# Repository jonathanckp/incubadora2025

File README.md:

# incubadora2025
proyecto incubadora de huevos - 2025

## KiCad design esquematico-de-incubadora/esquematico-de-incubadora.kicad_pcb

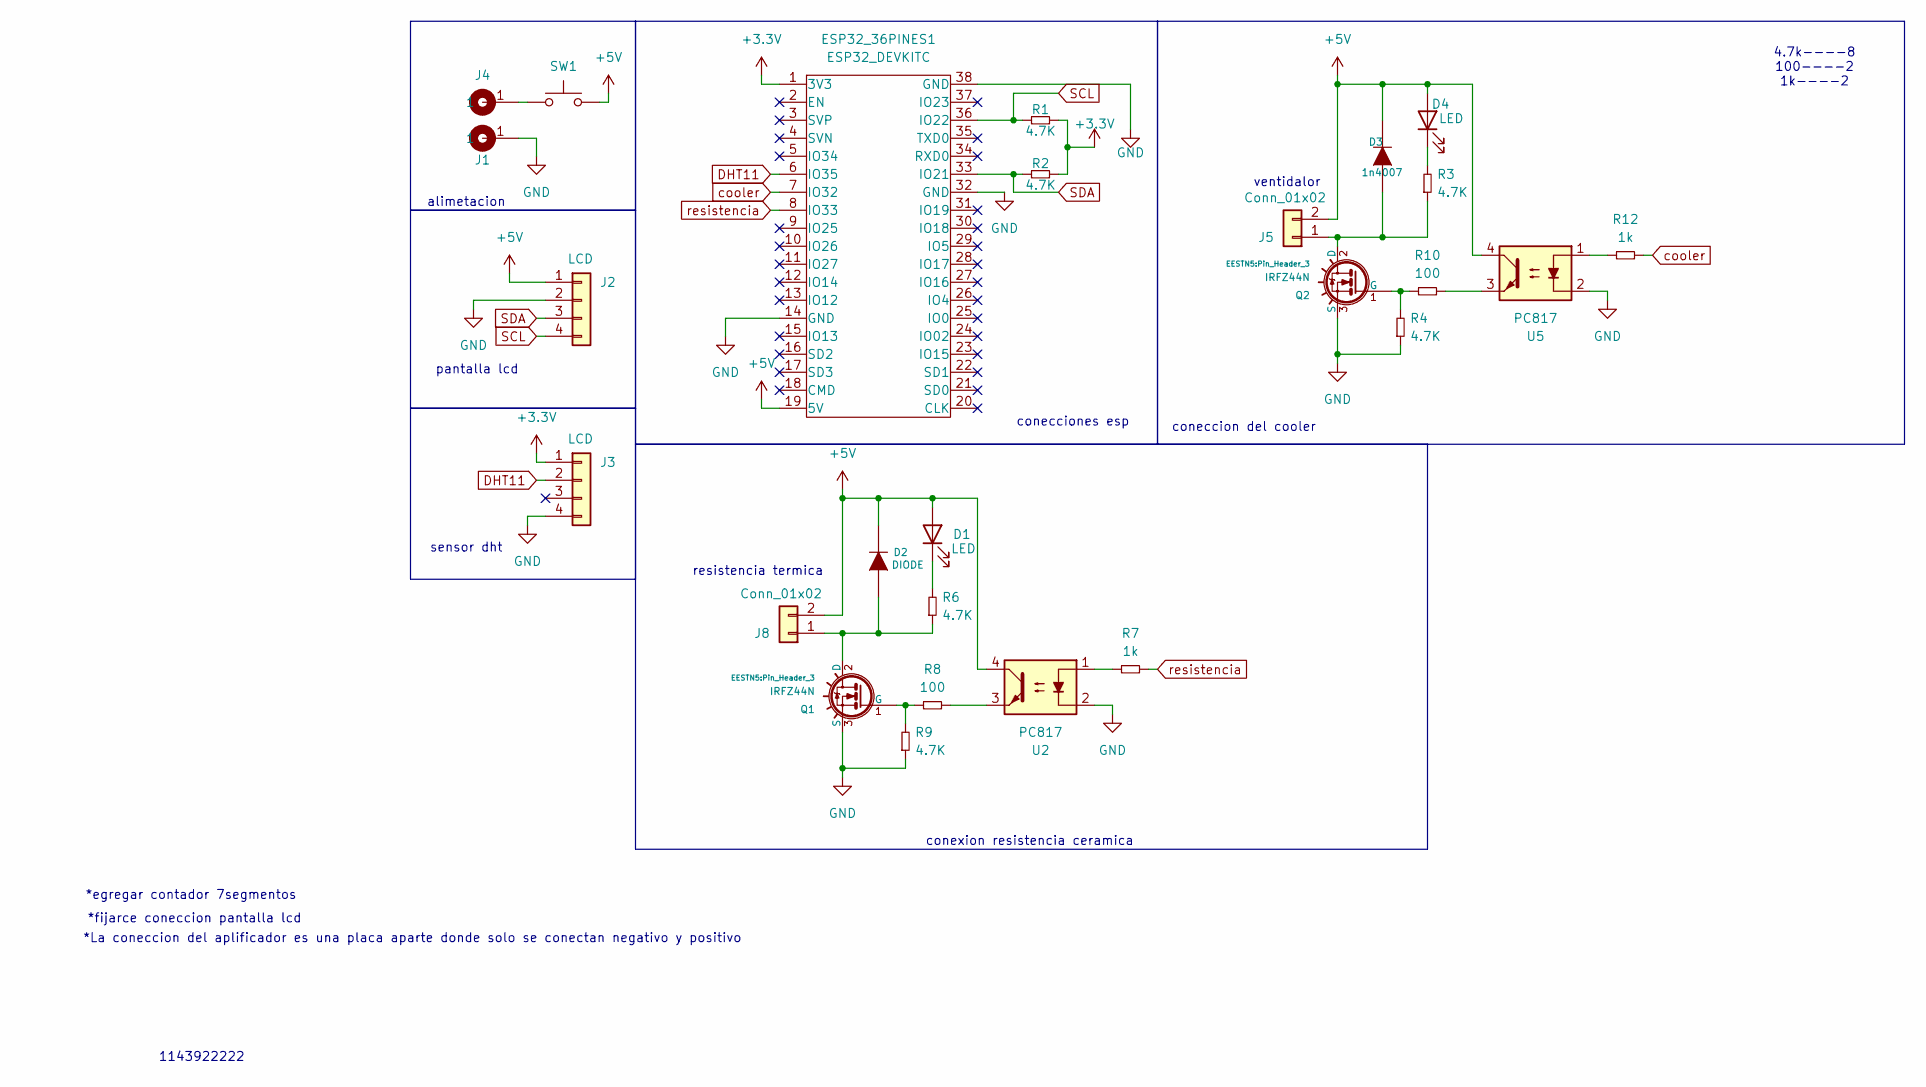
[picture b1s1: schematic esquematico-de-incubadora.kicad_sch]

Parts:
D1, D4: LED; led_5mm_clear
D2: DIODE; D_SMA
D3: 1n4007; D_SMA
ESP32_36PINES1: ESP32_DEVKITC; ESP32S
J1, J4: Cable_PAD; Cable_1,5mm
J2, J3: LCD; pin_strip_4
J5, J8: Conn_01x02; JST_EH_B2B-EH-A_1x02_P2.50mm_Vertical
Q1, Q2: IRFZ44N; Pin_Header_3
R1, R2, R4, R9: 4.7K; R_0805
R3, R6: 4.7K; R_1206
R7, R12: 1k; R_0805
R8, R10: 100; R_0805
SW1: SW_Push; Pin_Header_2
U2, U5: PC817; DIP-4_W7.62mm_LongPads

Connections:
+3.3V: ESP32_36PINES1.1 (3V3), J3.1, R1.2, R2.2
+5V: D1.2 (A), D2.2 (K), D3.2 (K), D4.2 (A), ESP32_36PINES1.19 (5V), J2.1, J5.2, J8.2, SW1.2, U2.4, U5.4
DHT11: ESP32_36PINES1.6 (IO35), J3.2
GND: ESP32_36PINES1.14 (GND), ESP32_36PINES1.32 (GND), ESP32_36PINES1.38 (GND), J1.1, J2.2, J3.4, Q1.3 (S), Q2.3 (S), R4.1, R9.1, U2.2, U5.2
unnamed: D1.1 (K), R6.2
unnamed: D2.1 (A), J8.1, Q1.2 (D), R6.1
unnamed: D3.1 (A), J5.1, Q2.2 (D), R3.1
unnamed: D4.1 (K), R3.2
unnamed: J4.1, SW1.1
unnamed: Q1.1 (G), R8.1, R9.2
unnamed: Q2.1 (G), R4.2, R10.1
unnamed: R7.1, U2.1
unnamed: R8.2, U2.3
unnamed: R10.2, U5.3
unnamed: R12.1, U5.1
SCL: ESP32_36PINES1.36 (IO22), J2.4, R1.1
SDA: ESP32_36PINES1.33 (IO21), J2.3, R2.1
cooler: ESP32_36PINES1.7 (IO32), R12.2
resistencia: ESP32_36PINES1.8 (IO33), R7.2

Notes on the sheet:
alimetacion
1143922222
resistencia termica
*egregar contador 7segmentos
coneccion del cooler
4.7k----8 100----2 1k----2
conexion resistencia ceramica
ventidalor
*La coneccion del aplificador es una placa aparte donde solo se conectan negativo y positivo
conecciones esp
*fijarce coneccion pantalla lcd
pantalla lcd
sensor dht

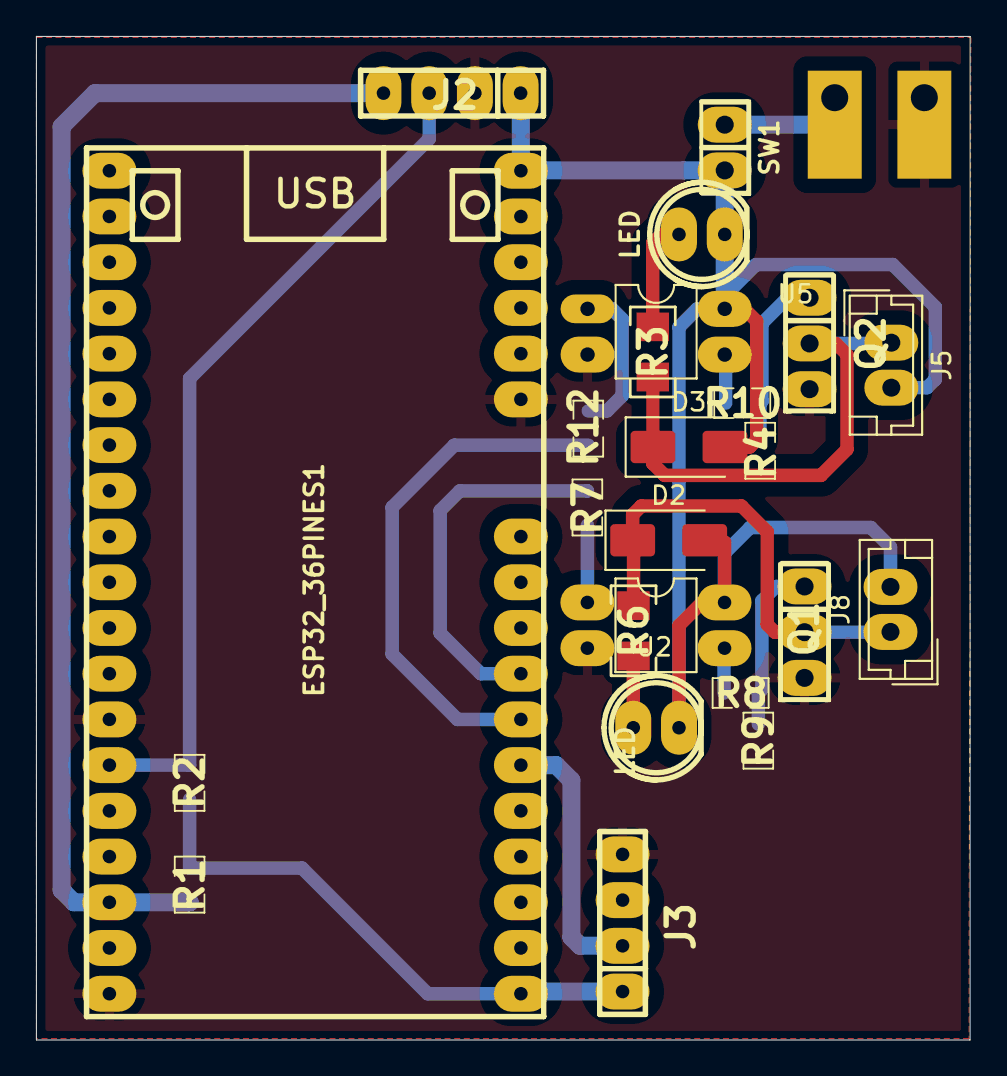
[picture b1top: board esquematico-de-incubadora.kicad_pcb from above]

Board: 2 copper layers, 51.9 x 55.8 mm, 26 parts (0 on the bottom side), 19 nets.

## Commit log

2025-04-07 Create Plan de proyecto
2025-04-07 Create componenetes
2025-04-07 Rename componenetes to componentes
2025-04-07 Update componentes
2025-04-21 Anteproyecto
2025-05-27 primera actualisacion
2025-05-27 modificacion
2025-06-17 Create dht11
2025-06-17 Create direccion I2c
